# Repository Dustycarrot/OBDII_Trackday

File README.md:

# OBD2 Dongle — Pico W

A removable OBD2 diagnostic reader built on a Raspberry Pi Pico W. Supports both K-Line (ISO 9141-2 / KWP2000) and CAN, covering vehicles from either protocol era.bare-chip hand-soldered build.

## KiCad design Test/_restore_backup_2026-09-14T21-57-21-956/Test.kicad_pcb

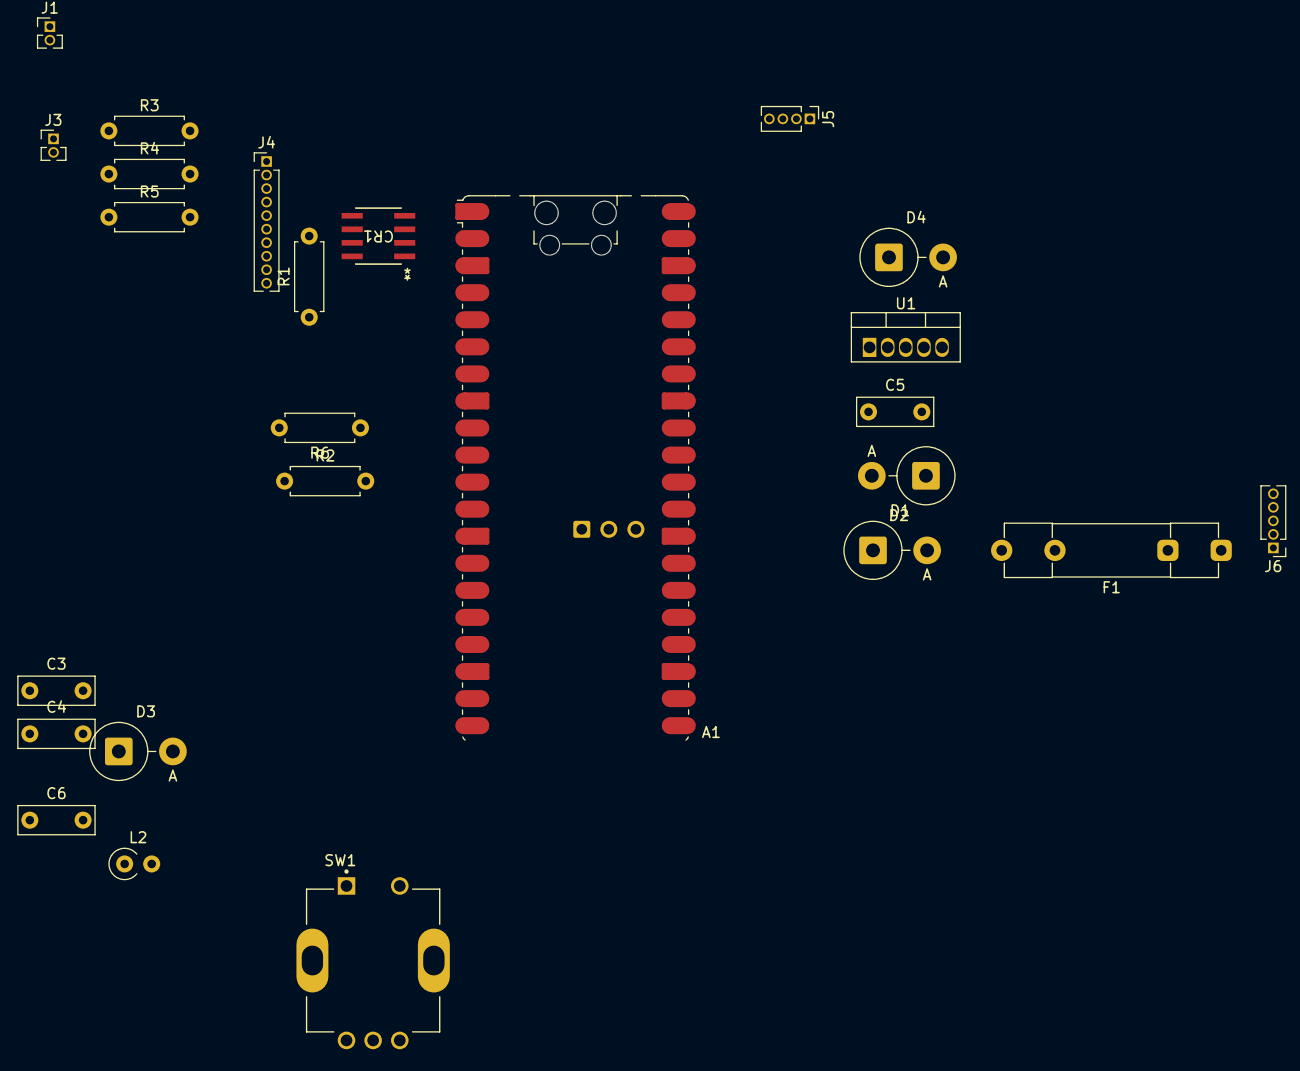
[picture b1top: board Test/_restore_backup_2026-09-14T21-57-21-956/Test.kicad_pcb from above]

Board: 2 copper layers, 25 parts (0 on the bottom side), 23 nets, no tracks yet.

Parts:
A1: RaspberryPi_Pico_W; RaspberryPi_Pico_W_SMD_HandSolder
C3, C4: 100n; C_Rect_L7.0mm_W2.5mm_P5.00mm
C5: 100u; C_Rect_L7.0mm_W2.5mm_P5.00mm
C6: 1000u; C_Rect_L7.0mm_W2.5mm_P5.00mm
CR1: E-L9637D; SO-8_STM
D1: 1N5408; D_DO-201_P5.08mm_Vertical_AnodeUp
D2: 1.5KE24A; D_DO-201_P5.08mm_Vertical_AnodeUp
D3: 1N4148; D_DO-201_P5.08mm_Vertical_AnodeUp
D4: MBR360; D_DO-201_P5.08mm_Vertical_AnodeUp
F1: Fuse; Fuseholder_Clip-5x20mm_Schurter_CQM_Inline_P20.60x5.00mm_D1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
J1, J3: Conn_01x02; PinHeader_1x02_P1.27mm_Vertical
J4: Conn_01x10; PinHeader_1x10_P1.27mm_Vertical
J5: Conn_01x04; PinHeader_1x04_P1.27mm_Vertical
J6: Conn_01x05; PinHeader_1x05_P1.27mm_Vertical
L2: 100u; L_Axial_L6.6mm_D2.7mm_P2.54mm_Vertical_Vishay_IM-2
R1: 510; R_Axial_DIN0207_L6.3mm_D2.5mm_P7.62mm_Horizontal
R2, R3, R4, R5, R6: 10k; R_Axial_DIN0207_L6.3mm_D2.5mm_P7.62mm_Horizontal
SW1: RotaryEncoder_Switch; XDCR_PEC11R-4220F-S0024
U1: LM2576T-5; TO-220-5_Vertical

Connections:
+3.3V: A1.36 (3V3), C4.1, CR1.3 (VCC), J4.1, R2.1, R3.1, R4.1, R5.1, R6.2
+5V: A1.39 (VSYS), C6.1, J5.1, L2.2, U1.4 (FB)
+12V: C3.1, C5.1, D1.1 (K), D2.2 (A2), D3.2 (A), R1.1, U1.1 (VIN)
/Battery_Power: F1.1, J6.1
/GPI02: A1.4 (GPIO2), CR1.2 (LO)
/GPIO0: A1.1 (GPIO0), CR1.4 (TX)
/GPIO1: A1.2 (GPIO1), CR1.1 (RX)
/GPIO6: A1.9 (GPIO6), R4.2
/GPIO7: A1.10 (GPIO7), R5.2, SW1.B
/GPIO8: A1.11 (GPIO8), R2.2, SW1.A
/GPIO16: A1.21 (GPIO16), J1.1, R6.1
/GPIO17: A1.22 (GPIO17), J3.1, R3.2
/K_Line: CR1.6 (K), J6.2, R1.2
/L_Line: CR1.8 (LI), J6.3
/SCA: A1.24 (GPIO18), J4.4
/SCL: A1.25 (GPIO19), J4.3
/SCL2: A1.27 (GPIO21), J5.4
/SDA: A1.26 (GPIO20), J5.3
GND: C3.2, C4.2, C5.2, C6.2, CR1.5 (GND), D2.1 (A1), D4.2 (A), J1.2, J3.2, J4.2, J4.10, J5.2, J6.4, J6.5, SW1.C, U1.3 (GND), U1.5 (~ON/OFF)
GNDS: A1.3 (GND), A1.8 (GND), A1.13 (GND), A1.18 (GND), A1.23 (GND), A1.28 (GND), A1.38 (GND)
unnamed: CR1.7 (VS), D3.1 (K)
unnamed: D1.2 (A), F1.2
unnamed: D4.1 (K), L2.1, U1.2 (OUT)

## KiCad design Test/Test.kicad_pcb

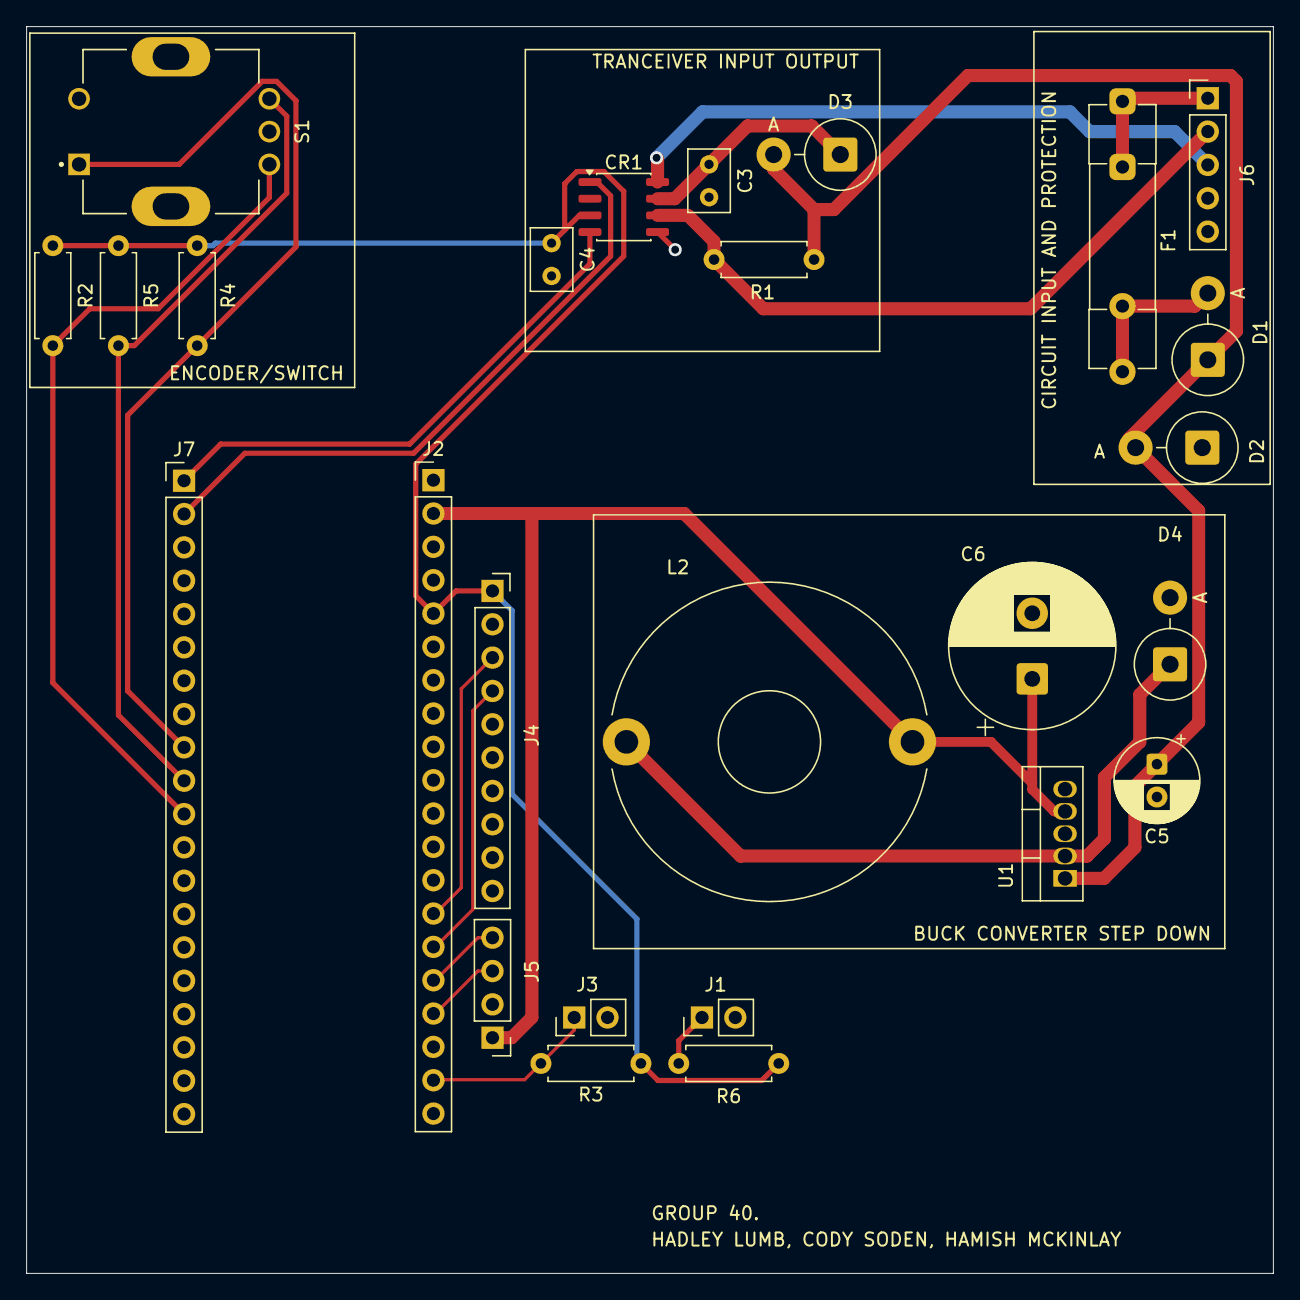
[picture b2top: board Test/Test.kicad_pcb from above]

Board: 2 copper layers, 95.0 x 95.0 mm, 26 parts (0 on the bottom side), 21 nets.

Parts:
C3, C4: 100n; C_Rect_L4.6mm_W3.0mm_P2.50mm_MKS02_FKP02
C5: 100u; CP_Radial_D6.3mm_P2.50mm
C6: 1000u; CP_Radial_D12.5mm_P5.00mm
CR1: E-L9637D; SO-8_3.9x4.9mm_P1.27mm
D1: 1N5408; D_DO-201_P5.08mm_Vertical_AnodeUp
D2: 1.5KE24A; D_DO-201_P5.08mm_Vertical_AnodeUp
D3: 1N4148; D_DO-201_P5.08mm_Vertical_AnodeUp
D4: MBR360; D_DO-201_P5.08mm_Vertical_AnodeUp
F1: Fuse; Fuseholder_Clip-5x20mm_Schurter_CQM_Inline_P20.60x5.00mm_D1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
J1, J3: Conn_01x02; PinHeader_1x02_P2.54mm_Vertical
J2, J7: Conn_01x20; PinHeader_1x20_P2.54mm_Vertical
J4: Conn_01x10; PinSocket_1x10_P2.54mm_Vertical
J5: Conn_01x04; PinHeader_1x04_P2.54mm_Vertical
J6: Conn_01x05; PinHeader_1x05_P2.54mm_Vertical
L2: 100u; L_Toroid_Horizontal_D24.1mm_P21.80mm_Bourns_2200
R1: 510; R_Axial_DIN0207_L6.3mm_D2.5mm_P7.62mm_Horizontal
R2, R3, R4, R5, R6: 10k; R_Axial_DIN0207_L6.3mm_D2.5mm_P7.62mm_Horizontal
S1: PEC11R-4220F-S0024; XDCR_PEC11R-4220F-S0024
U1: LM2576T-5; TO-220-5_Vertical

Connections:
+3.3V: C4.1, CR1.3 (VCC), J2.5, J4.1, R2.2, R3.1, R4.1, R5.2, R6.2
+5V: C6.1, J2.2, J5.1, L2.2, U1.4 (FB)
+12V: C5.1, D1.1 (K), D2.2 (A2), D3.2 (A), R1.1, U1.1 (VIN)
/Battery_Power: F1.1, J6.1
/GPIO0: CR1.4 (TX), J7.1
/GPIO1: CR1.1 (RX), J7.2
/GPIO6: J7.9, R4.2, S1.1
/GPIO7: J7.10, R5.1, S1.B
/GPIO8: J7.11, R2.1, S1.A
/GPIO16: J1.1, R6.1
/GPIO17: J2.19, J3.1, R3.2
/K_Line: CR1.6 (K), J6.2, R1.2
/L_Line: CR1.8 (LI), J6.3
/SCA: J2.15, J4.4
/SCL: J2.14, J4.3
/SCL2: J2.16, J5.4
/SDA: J2.17, J5.3
GND: C3.2, C4.2, C5.2, C6.2, CR1.5 (GND), D2.1 (A1), D4.2 (A), J1.2, J2.3, J2.13, J2.18, J3.2, J4.2, J4.10, J5.2, J6.4, J6.5, J7.3, J7.8, J7.13, J7.18, S1.2, S1.C (COM), S1.SH1 (SHIELD), S1.SH2 (SHIELD), U1.3 (GND), U1.5 (~ON/OFF)
unnamed: C3.1, CR1.7 (VS), D3.1 (K)
unnamed: D1.2 (A), F1.2
unnamed: D4.1 (K), L2.1, U1.2 (OUT)
